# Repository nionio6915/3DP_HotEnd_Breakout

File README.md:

# 3DP_HotEnd_Breakout
PCB breakout board to tidy up the wiring at the hotend of a 3D Printer. <br>

Details: 
Traces on top & bottom.  
Hot End traces are estaimted to carry a maximum current of 5A at 2C temp rise.  <br>
This should in theory handle up to a 12v-50W heater using a 2-layer PCB with 1oz copper on each face.<br>   
Solder pads for SMT components are prortioned for hand soldeirng. SMT componnents are optional Pads are sized for 1206 sized components, but can be populated with as small as 0603's. <br>   

KiCAD generated .step file included for your convenience. <br>

Connectors provided for: <br>
E0 hot end, with screw terminals, same connector as on Duet2/3 hardware<br>
THERM themrmistor, JST XH / male header pins<br> 
FAN0: 1  hot end cooling fan, JST XH  / male header pins<br> 
FAN1: 2 part cooling fans, JST XH / male header pins<br>  
1 3-pin Z Probe connection <br>
1 2-pin LED connection<br>
1 2-pin AUX connection<br>  

LED's are optional. I like the convenience of seeing an indicator when observing my printer via webcam. I can not see the fans when they are running, so I added traces for indicator LED's. Similalry, not being abel to see the controller's LED's I added an indicator LED tied to the hotend and the LED circuit.<br>   

One addtional JST connector is provided in the event you are using a BL_Touch and require 5 conductors, 3+2. Else, the JST can be used for general purpose LED lighting of the carraige.<br>      

Male solder headers are shown, but thru-hole soldering of the wires directly to the board is prefered.<br>   

M3 screw holes are provided in the corners frou mounting, as well as 2 slotted holes for a zip-tie to secure the board/wires. <br> 

Board dimensions are approximteley 48mm x 24mm (1.87x0.93 inch)<br>  
As of 11/2020, $8.65 for 3 boards fabbed at OSHPark. <br>  

BOM:<br>   
5, 2-Pin JST XH_B2B-AM sockets  
    <https://octopart.com/b2b-xh-a%28lf%29%28sn%29-jst-7424860?r=sp>  
2, 3.5mm pitch screw terminal (Phoenix Contact 1751248) or equivalent  
    <https://octopart.com/search?q=Phoenix+Contact+1751248&currency=USD&specs=0>  
4, 0603 -1206 SMD Resistors, 760Ohm to 1KOhm  
    <https://octopart.com/search?q=0603+resistor&currency=USD&specs=0&resistance=1000>  
4, 0805 -1206 LED's of your choosing  
    <https://octopart.com/search?q=0805+LED&currency=USD&specs=0>  
6, 2 pin Male headers  
2, 3 pin Male headers

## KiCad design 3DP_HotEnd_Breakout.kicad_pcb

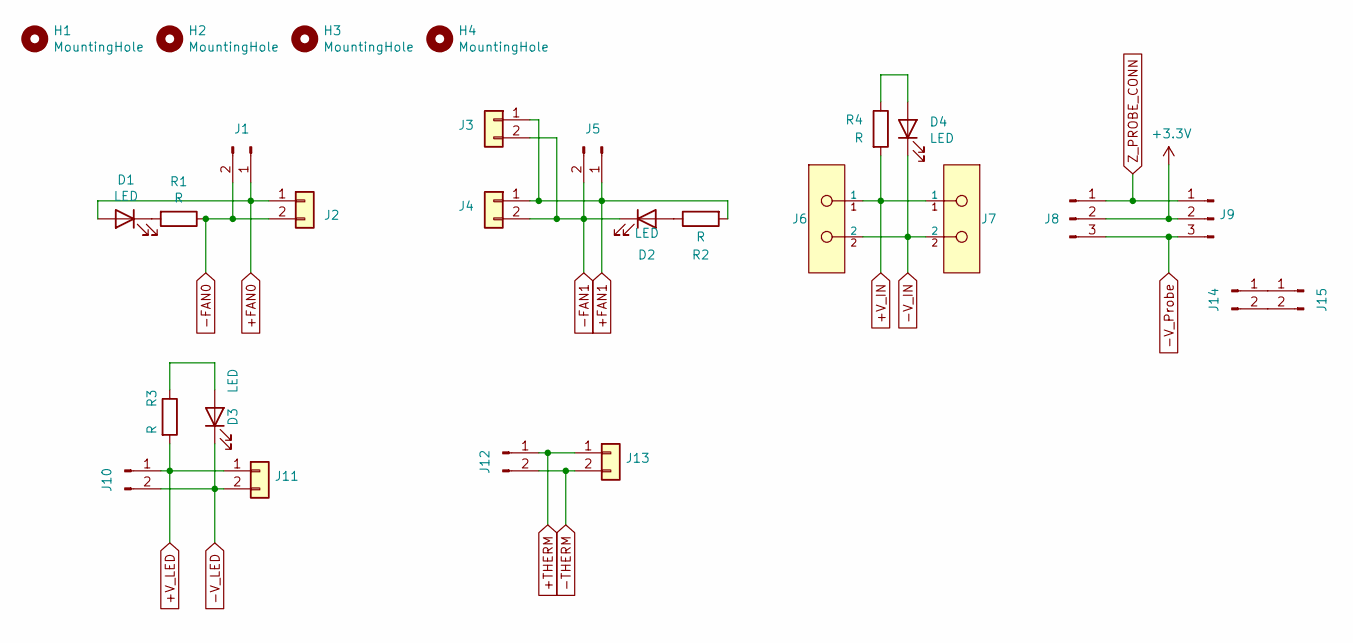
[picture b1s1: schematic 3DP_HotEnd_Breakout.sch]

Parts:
D1, D2, D3, D4: LED; LED_1206_3216Metric_Pad1.42x1.75mm_HandSolder
H1, H2, H3, H4: MountingHole; MountingHole_3.2mm_M3
J1, J5, J10, J12, J14, J15: Conn_01x02_Male; PinHeader_1x02_P2.54mm_Vertical
J2, J3, J4, J11, J13: Conn_01x02; JST_XH_B2B-XH-AM_1x02_P2.50mm_Vertical_DJP
J6, J7: 1751248; Phoenix_Contact-1751248-0-0-0; current rating 13.5A; voltage rating 200V; mouser part number 651-1751248; digikey description CONN TERM BLOCK 2POS 3.5MM
J8, J9: Conn_01x03_Male; PinHeader_1x03_P2.54mm_Vertical
R1, R2, R3, R4: R; R_1206_3216Metric_Pad1.30x1.75mm_HandSolder

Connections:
+3V3: J8.2, J9.2
+FAN0: D1.2 (A), J1.1, J2.1
+FAN1: J3.1, J4.1, J5.1, R2.2
+THERM: J12.1, J13.1
+V_IN: J6.1, J7.1, R4.2
+V_LED: J10.1, J11.1, R3.2
-FAN0: J1.2, J2.2, R1.1
-FAN1: D2.1 (K), J3.2, J4.2, J5.2
-THERM: J12.2, J13.2
-V_IN: D4.1 (K), J6.2, J7.2
-V_LED: D3.1 (K), J10.2, J11.2
-V_Probe: J8.3, J9.3
unnamed: D1.1 (K), R1.2
unnamed: D2.2 (A), R2.1
unnamed: D3.2 (A), R3.1
unnamed: D4.2 (A), R4.1
unnamed: J14.1, J15.1
unnamed: J14.2, J15.2
Z_PROBE_CONN: J8.1, J9.1

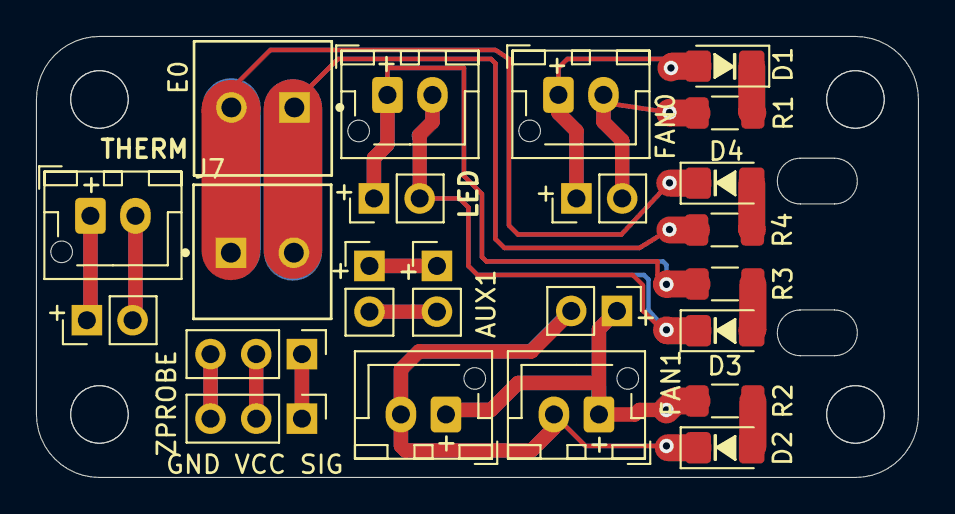
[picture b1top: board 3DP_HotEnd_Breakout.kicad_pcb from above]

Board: 2 copper layers, 49.0 x 24.5 mm, 27 parts (0 on the bottom side), 19 nets.

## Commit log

2020-11-08 Initial Upload
    Initial Upload of PCB Design
2020-11-09 Initial commit
    Initial commit
2020-11-09 Fix jumper label alignements
    Fix jumper label alignements
2020-11-09 updated BOM & Details
2020-11-24 REV1
2020-11-24 revised SMT pads
2020-11-24 step
